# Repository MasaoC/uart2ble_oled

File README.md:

# uart2ble_oled

- UARTを受信し、OLEDおよびBLEに送信するArduinoプログラムです。
- ESP32C3 XIAO用に作成されています。nrf52840用もありますが飛距離が最大15m程度なのでTFでは使えません。
- リレー以外にはOLEDに表示する機能もついています。UART -> XIAO(ESP32C3) -> SSD1306 and BLE.
- 受信のUARTは38400Baud. OLED(SSD1306)とはI2Cで通信する。
- UARTで受信したデータのうち、#で始まる文字列のみを、BLE Nordic UARTで送信する。
- MacBookAirで受信してPythonでグラフ化するコードも公開しています。[ble_plotter](https://github.com/MasaoC/ble_plotter)はこちら。
- 詳細情報が欲しい方はメールからどうぞ。

## 仕様書
- [BLEOLED_nrf52840](https://github.com/MasaoC/uart2ble_oled/blob/main/doc/UARTtoOLED%E5%9F%BA%E6%9D%BFv1%20%E4%BB%95%E6%A7%98%E6%9B%B8.pdf)
- [BLEOLEDv2_ESP32C3](https://github.com/MasaoC/uart2ble_oled/blob/main/doc/UARTtoOLED%E5%9F%BA%E6%9D%BFv2%20%E4%BB%95%E6%A7%98%E6%9B%B8.pdf)

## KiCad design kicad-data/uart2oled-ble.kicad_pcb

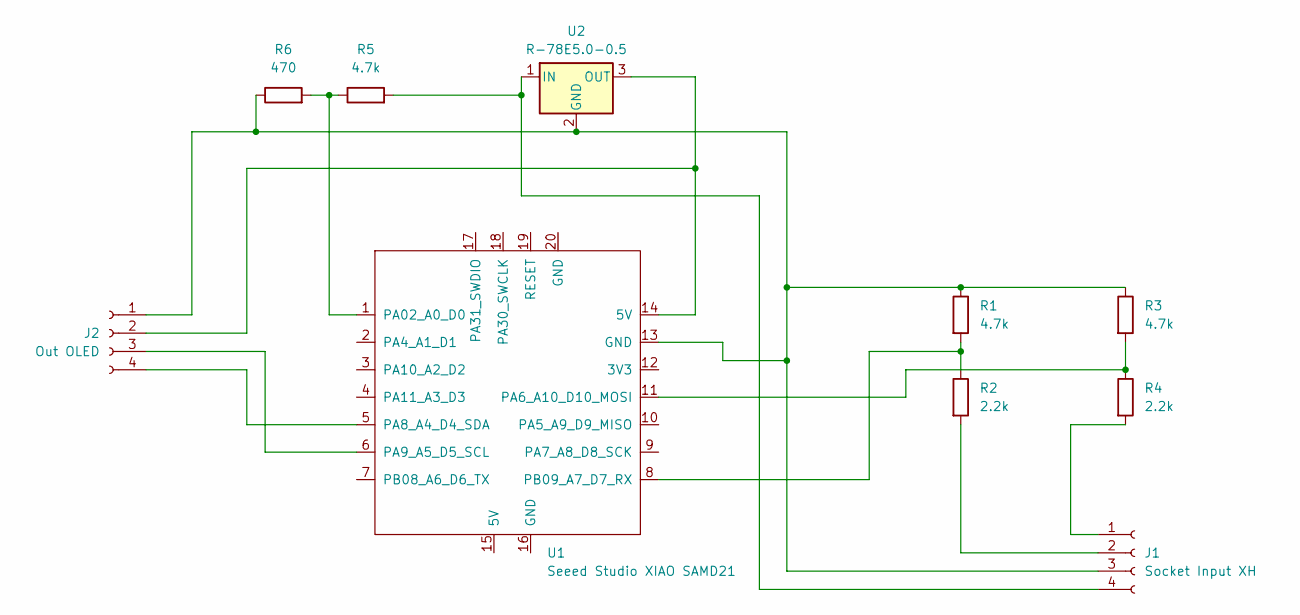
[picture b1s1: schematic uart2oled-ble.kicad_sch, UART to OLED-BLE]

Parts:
J1: Socket Input XH; JST_XH_B4B-XH-A_1x04_P2.50mm_Vertical
J2: Out OLED; PinHeader_1x04_P2.54mm_Vertical
R1, R3, R5: 4.7k; R_0603_1608Metric_Pad0.98x0.95mm_HandSolder
R2, R4: 2.2k; R_0603_1608Metric_Pad0.98x0.95mm_HandSolder
R6: 470; R_0603_1608Metric_Pad0.98x0.95mm_HandSolder
U1: Seeed Studio XIAO SAMD21; XIAO-SAMD21-RP2040-14P-2.54-21X17.8MM (Seeeduino XIAO)
U2: R-78E5.0-0.5; Converter_DCDC_RECOM_R-78E-0.5_THT

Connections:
unnamed: J1.1, R4.2
unnamed: J1.2, R2.2
unnamed: J1.3, J2.1, R1.1, R3.1, R6.1, U1.13 (GND), U2.2 (GND)
unnamed: J1.4, R5.2, U2.1 (IN)
unnamed: J2.2, U1.14 (5V), U2.3 (OUT)
unnamed: J2.3, U1.6 (PA9_A5_D5_SCL)
unnamed: J2.4, U1.5 (PA8_A4_D4_SDA)
unnamed: R5.1, R6.2, U1.1 (PA02_A0_D0)
unnamed: R3.2, R4.1, U1.11 (PA6_A10_D10_MOSI)
unnamed: R1.2, R2.1, U1.8 (PB09_A7_D7_RX)

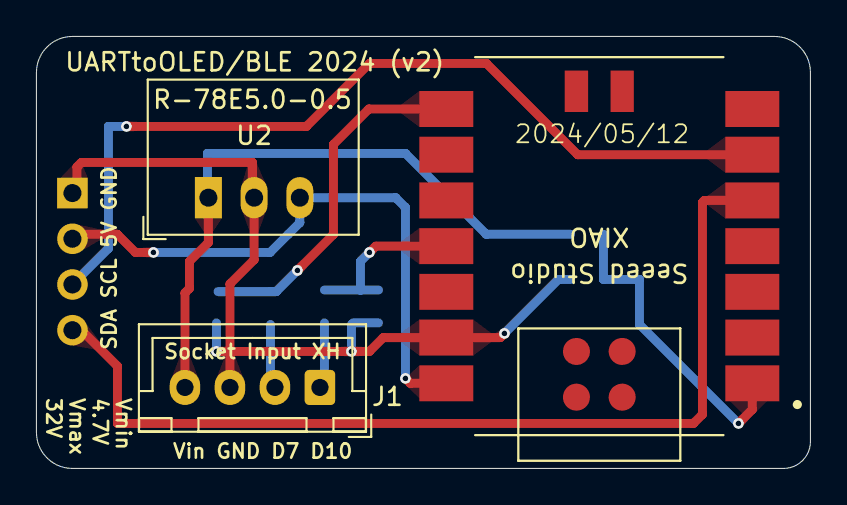
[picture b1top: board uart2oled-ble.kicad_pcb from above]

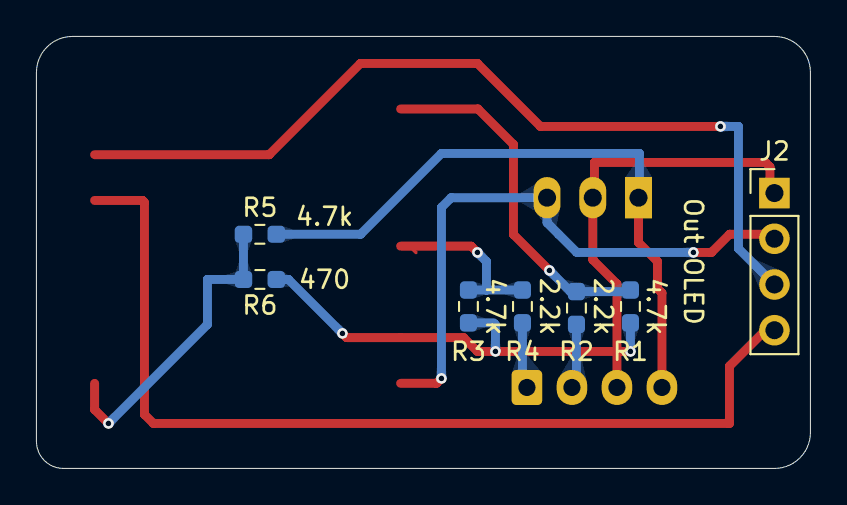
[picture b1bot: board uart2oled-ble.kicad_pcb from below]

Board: 2 copper layers, 43.0 x 24.0 mm, 10 parts (7 on the bottom side), 10 nets.

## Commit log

2024-05-28 Create BLEOLEDv2.ino
    ver 1.0
2024-05-29 BLE Relay module file added
    Using two XIAO(ESP32C3) master and relay, longer range communication can be achieved.
2024-05-30 adding new folder for nrf52840 and update program
    nrf52840 file added.
    update for esp32 3.0.0
2024-06-03 仕様書追加
    PDF
2024-06-03 Add kicad data
    kicad for v2 board
2024-06-04 Add PCB image
2025-04-04 Minor updates due to esp32 update.
    ・From std::string to String
    ・I2C detection implemented.
